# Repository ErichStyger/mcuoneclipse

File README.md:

mcuoneclipse
============

McuOnEclipse Processor Expert components and example projects.
C:\ProgramData\Processor Expert\CWMCU_PE5_00\beans

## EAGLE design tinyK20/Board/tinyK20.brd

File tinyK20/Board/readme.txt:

tinyK20 project files for Eagle CAD.
Links:
- https://mcuoneclipse.com/category/boards/tinyk20/
- https://mcuoneclipse.com/2015/11/17/production-tinyk20-boards-arrived/
- https://mcuoneclipse.com/2015/06/17/tinyk20-new-board-with-micro-sd-card/

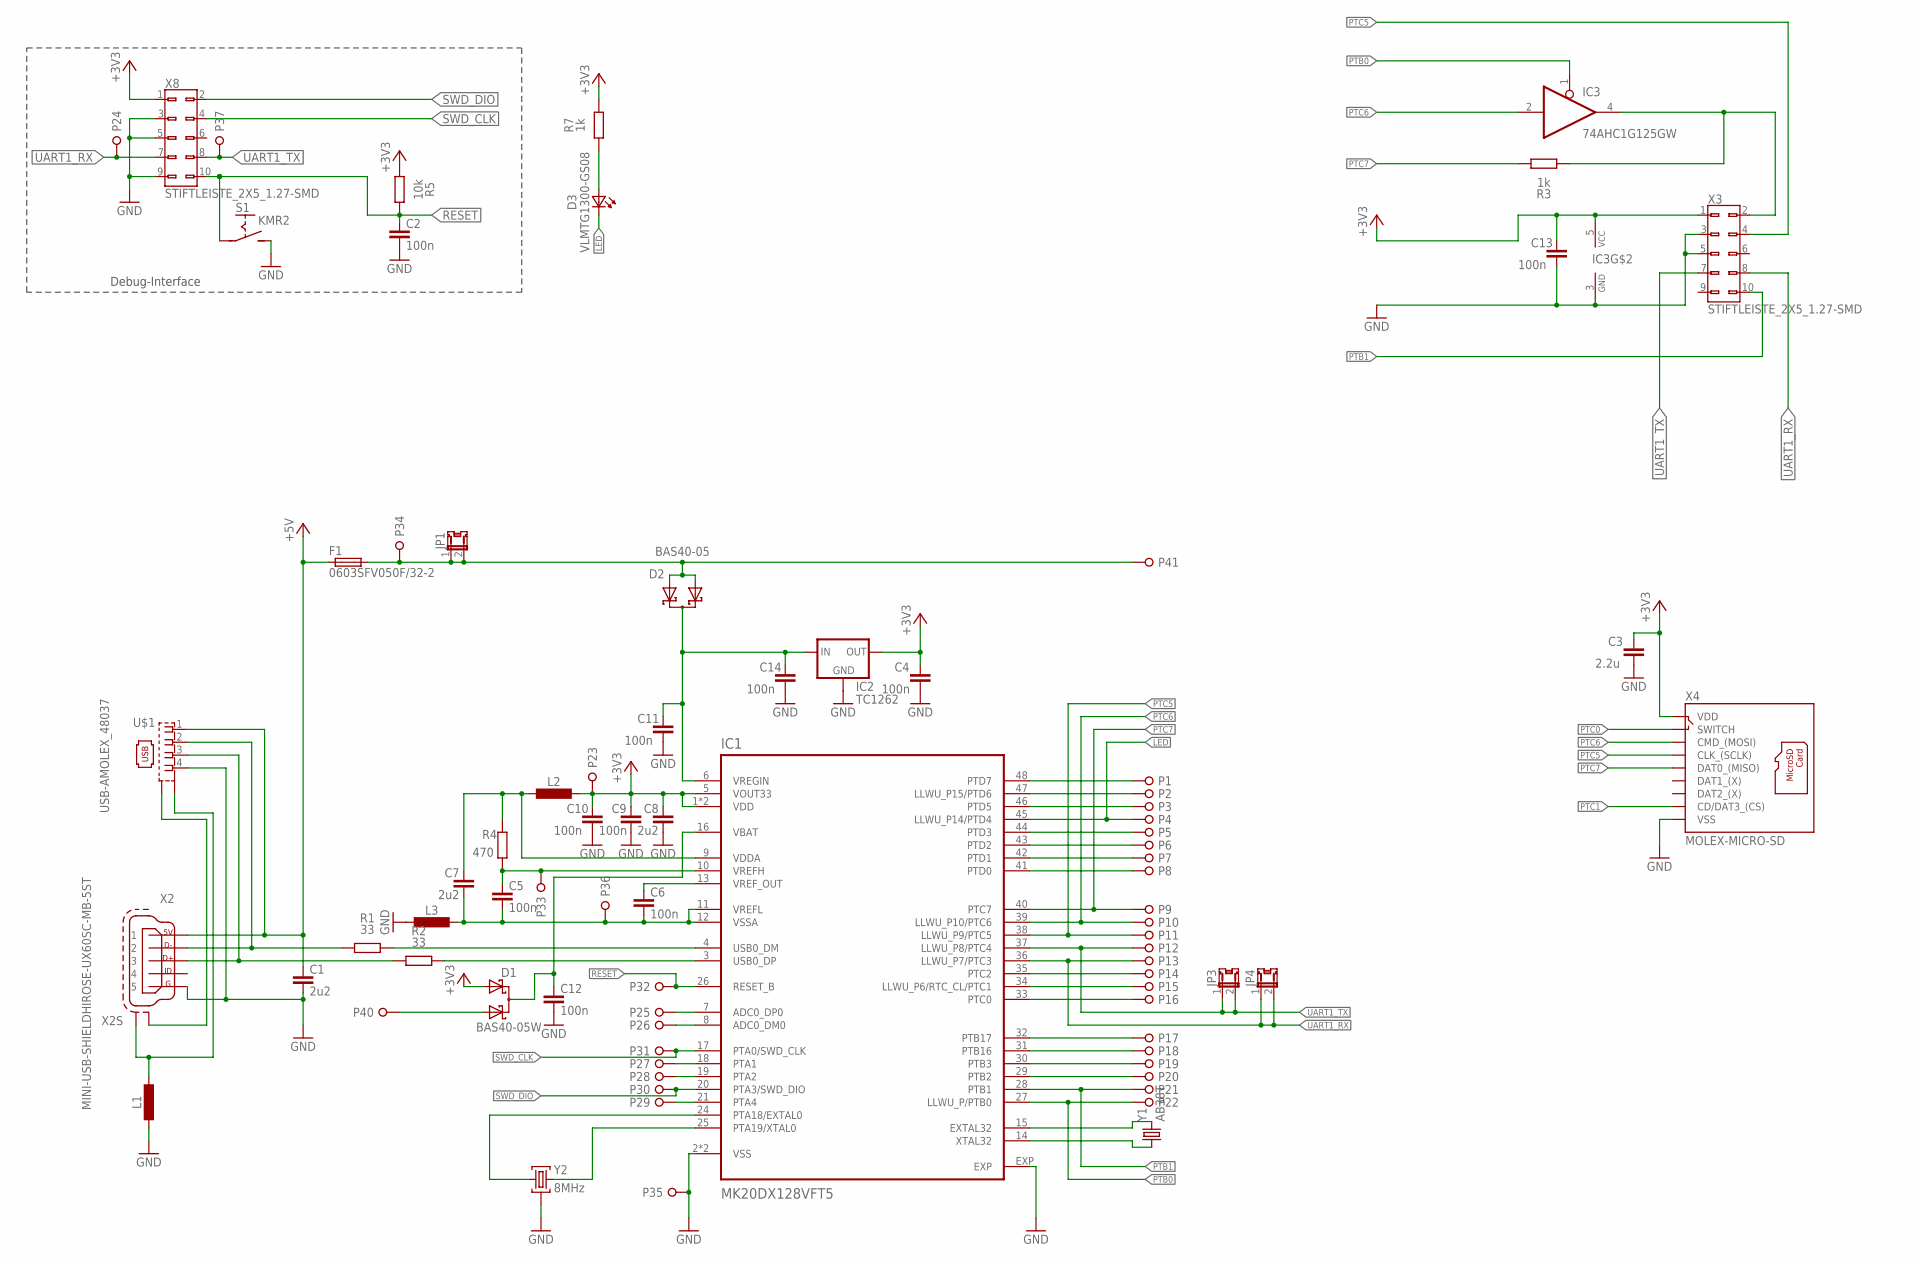
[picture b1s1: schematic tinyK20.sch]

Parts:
C1, C7, C8: 2u2; C0603-R
C2, C4, C5, C6, C9, C10, C11, C12, C13, C14: 100n; C0603-R
C3: 2.2u; C0603-R
D1: BAS40-05W; SOT-323
D2: BAS40-05; SOT-23
D3: VLMTG1300-GS08; D0603-R
F1: 0603SFV050F/32-2; 0603-R
IC1: MK20DX128VFT5; QFN48
IC2: TC1262; SOT-223
IC3: 74AHC1G125GW; SOT-353
JP1, JP3, JP4: JP1-SMD-1.2X1.8; JP-SMD-1.2X1.8
L1, L2, L3: L; L0603-R
P1, P2, P3, P4, P5, P6, P7, P8, P9, P10, P11, P12, P13, P14, P15, P16, P17, P18, P19, P20, P21, P22, P23, P24, P25, P26, P27, P28, P29, P30, P31, P32, P33, P34, P35, P36, P37, P40, P41: SOLDERPAD; SOLDERPAD_TH_0.9
R1, R2: 33; R0603-R
R3, R7: 1k; R0603-R
R4: 470; R0603-R
R5: 10k; R0603-R
S1: KMR2; SWITCH-KMR-SERIES
U$1: USB-AMOLEX_48037; USB-A-MOLEX_48037
X2: MINI-USB-SHIELDHIROSE-UX60SC-MB-5ST; USB-MINI-B-HORIZ_HIROSE-UX60SC-MB-5ST
X3, X8: STIFTLEISTE_2X5_1.27-SMD; STIFTLEISTE_2X5_1.27_SMD
X4: MOLEX-MICRO-SD; SD-105027-001
Y1: AB38T; CRYSTAL-AB38T
Y2: 8MHz; CSTCE

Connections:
+3V3: C3.1, C4.1, C8.1, C9.1, C10.1, C13.1, D1.1 (A), IC1.1 (VDD), IC1.5 (VOUT33), IC1.22 (VDD), IC2.3 (OUT), IC3.5 (VCC), L2.2, P23.1, R5.1, R7.2, X3.1, X4.P4 (VDD), X8.1
+5V: C1.1, F1.1, U$1.1, X2.1
GND: C1.2, C2.2, C3.2, C4.2, C8.2, C9.2, C10.2, C11.2, C12.2, C13.2, C14.2, IC1.2 (VSS), IC1.23 (VSS), IC1.EXP, IC2.2 (GND), IC2.4 (GND), IC3.3 (GND), L1.1, L3.1, P35.1, S1.3 (S), S1.4 (S), U$1.4, X2.5, X3.3, X3.5, X4.P6 (VSS), X8.3, X8.5, X8.9, Y2.2
LED: D3.2 (K), IC1.45 (LLWU_P14/PTD4), P4.1
unnamed: R1.1, U$1.2, X2.2
unnamed: D1.2 (A), P40.1
unnamed: C5.2, C6.2, C7.2, IC1.11 (VREFL), IC1.12 (VSSA), L3.2, P36.1
unnamed: R2.1, U$1.3, X2.3
unnamed: C6.1, IC1.13 (VREF_OUT)
unnamed: IC1.4 (USB0_DM), R1.2
unnamed: C5.1, IC1.10 (VREFH), P33.1, R4.1
unnamed: IC1.3 (USB0_DP), R2.2
unnamed: IC1.24 (PTA18/EXTAL0), Y2.1
unnamed: IC1.25 (PTA19/XTAL0), Y2.3
unnamed: C7.1, IC1.9 (VDDA), L2.1, R4.2
unnamed: IC1.48 (PTD7), P1.1
unnamed: IC1.47 (LLWU_P15/PTD6), P2.1
unnamed: IC1.46 (PTD5), P3.1
unnamed: U$1.S2A (S2), U$1.S2B (S2), X2.S1
unnamed: C11.1, C14.1, D2.3 (COMMON), IC1.6 (VREGIN), IC2.1 (IN)
unnamed: D3.1 (A), R7.1
unnamed: IC1.44 (PTD3), P5.1
unnamed: C12.1, D1.3 (COMMON), IC1.16 (VBAT)
unnamed: IC1.43 (PTD2), P6.1
unnamed: IC1.42 (PTD1), P7.1
unnamed: IC1.41 (PTD0), P8.1
unnamed: D2.1 (A), D2.2 (A), F1.2, JP1.1, JP1.2, P34.1, P41.1
unnamed: IC3.4 (O), R3.1, X3.2
unnamed: IC1.35 (PTC2), P14.1
unnamed: IC1.32 (PTB17), P17.1
unnamed: IC1.31 (PTB16), P18.1
unnamed: IC1.30 (PTB3), P19.1
unnamed: IC1.29 (PTB2), P20.1
unnamed: IC1.15 (EXTAL32), Y1.2 (3)
unnamed: IC1.14 (XTAL32), Y1.1
unnamed: IC1.21 (PTA4), P29.1
unnamed: IC1.19 (PTA2), P28.1
unnamed: IC1.18 (PTA1), P27.1
unnamed: IC1.8 (ADC0_DM0), P26.1
unnamed: IC1.7 (ADC0_DP0), P25.1
unnamed: L1.2, U$1.S1A (S1), U$1.S1B (S1), X2.S2
PTB0: IC1.27 (LLWU_P/PTB0), IC3.1 (OE), P22.1
PTB1: IC1.28 (PTB1), P21.1, X3.10
PTC0: IC1.33 (PTC0), P16.1, X4.G1 (SWITCH)
PTC1: IC1.34 (LLWU_P6/RTC_CL/PTC1), P15.1, X4.P2 (CD/DAT3_(CS))
PTC5: IC1.38 (LLWU_P9/PTC5), P11.1, X3.4, X4.P5 (CLK_(SCLK))
PTC6: IC1.39 (LLWU_P10/PTC6), IC3.2 (I), P10.1, X4.P3 (CMD_(MOSI))
PTC7: IC1.40 (PTC7), P9.1, R3.2, X4.P7 (DAT0_(MISO))
RESET: C2.1, IC1.26 (RESET_B), P32.1, R5.2, S1.1 (C), S1.2 (C), X8.10
SWD_CLK: IC1.17 (PTA0/SWD_CLK), P31.1, X8.4
SWD_DIO: IC1.20 (PTA3/SWD_DIO), P30.1, X8.2
UART1_RX: IC1.36 (LLWU_P7/PTC3), JP4.1, JP4.2, P13.1, P24.1, X3.8, X8.7
UART1_TX: IC1.37 (LLWU_P8/PTC4), JP3.1, JP3.2, P12.1, P37.1, X3.7, X8.8

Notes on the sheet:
Debug-Interface

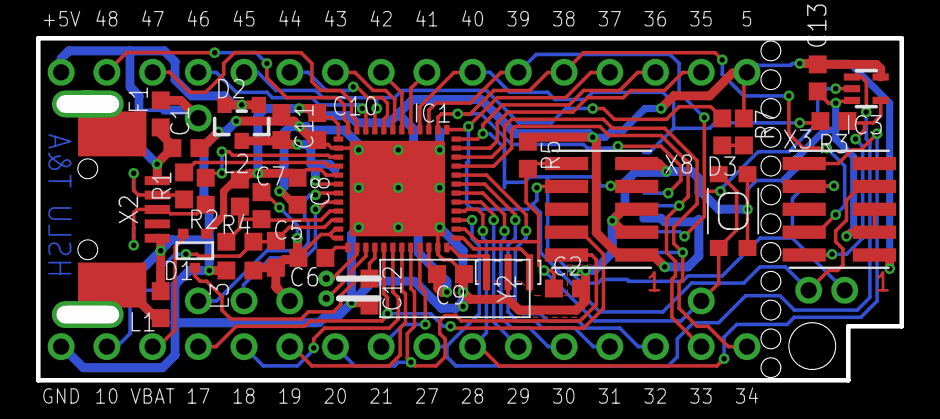
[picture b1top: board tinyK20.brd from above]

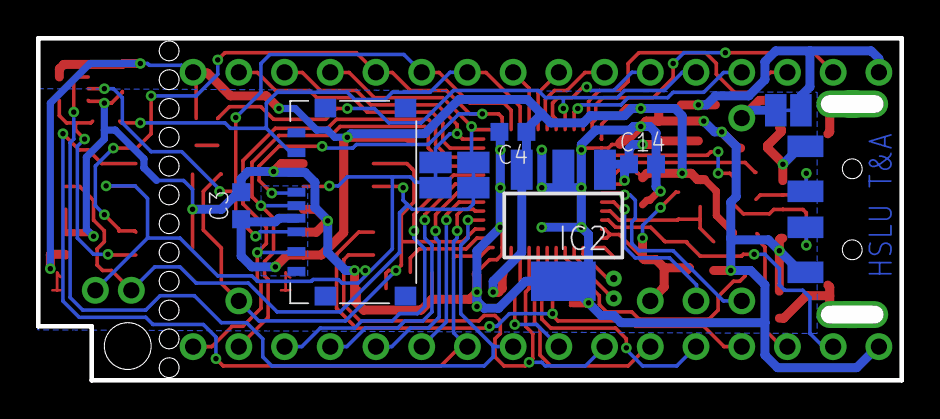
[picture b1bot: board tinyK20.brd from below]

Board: 2 copper layers, 48.0 x 19.0 mm, 80 parts (9 on the bottom side), 53 nets.

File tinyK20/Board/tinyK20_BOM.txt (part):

Part Value                               Device                              Package                               Description                      MFR    MFR_PART-NO   MOUSER_PART-NO   
C1   2u2                                 C0603                               C0603-R                               Capacitor                                                              
C2   100n                                C0603                               C0603-R                               Capacitor                                                              
C3   2.2u                                C0603                               C0603-R                               Capacitor                                                              
C4   100n                                C0603                               C0603-R                               Capacitor                                                              
C5   100n                                C0603                               C0603-R                               Capacitor                                                              
C6   100n                                C0603                               C0603-R                               Capacitor                                                              
C7   2u2                                 C0603                               C0603-R                               Capacitor                                                              
C8   2u2                                 C0603                               C0603-R                               Capacitor                                                              
C9   100n                                C0603                               C0603-R                               Capacitor                                                              
C10  100n                                C0603                               C0603-R                               Capacitor                                                              
C11  100n                                C0603                               C0603-R                               Capacitor                                                              
C12  100n                                C0603                               C0603-R                               Capacitor                                                              
C13  100n                                C0603                               C0603-R                               Capacitor                                                              
C14  100n                                C0603                               C0603-R                               Capacitor                                                              
D1   BAS40-05W                           BAS40-05W                           SOT-323                               Schottky Diode Common Cathode                                          
D2   BAS40-05                            BAS40-05                            SOT-23                                Schottky Diode Common Cathode                                          
D3   VLMTG1300-GS08                      VLMTG1300-GS08                      D0603-R                               Vishay 0603 Highbright ChipLED                                         
F1   0603SFV050F/32-2                    0603SFV050F/32-2                    0603-R                                0603 Very Fast-Acting Chip Fuses                                       
IC1  MK20DX128VFT5                       MK20DX128VFT5                       QFN48                                                                                                        
IC2  TC1262                              TC1262                              SOT-223                               500mA Fixed Output CMOS LDO                                            
IC3  74AHC1G125GW                        74AHC1G125GW                        SOT-353                                                                                                      
JP1  JP1-SMD-1.2X1.8                     JP1-SMD-1.2X1.8                     JP-SMD-1.2X1.8                        JUMPER                                                                 
L1                                       L                                   L0603-R                               Inductor                                                               
L2                                       L                                   L0603-R                               Inductor                                                               
L3                                       L                                   L0603-R                               Inductor                                                               
P1   SOLDERPAD                           SOLDERPAD                           SOLDERPAD_TH_0.9                                                                                             
P2   SOLDERPAD                           SOLDERPAD                           SOLDERPAD_TH_0.9                                                                                             
P3   SOLDERPAD                           SOLDERPAD                           SOLDERPAD_TH_0.9                                                                                             
P4   SOLDERPAD                           SOLDERPAD                           SOLDERPAD_TH_0.9                                                                                             
P5   SOLDERPAD                           SOLDERPAD                           SOLDERPAD_TH_0.9                                                                                             
P6   SOLDERPAD                           SOLDERPAD                           SOLDERPAD_TH_0.9                                                                                             
P7   SOLDERPAD                           SOLDERPAD                           SOLDERPAD_TH_0.9                                                                                             
P8   SOLDERPAD                           SOLDERPAD                           SOLDERPAD_TH_0.9                                                                                             
P9   SOLDERPAD                           SOLDERPAD                           SOLDERPAD_TH_0.9                                                                                             
P10  SOLDERPAD                           SOLDERPAD                           SOLDERPAD_TH_0.9                                                                                             
P11  SOLDERPAD                           SOLDERPAD                           SOLDERPAD_TH_0.9                                                                                             
P12  SOLDERPAD                           SOLDERPAD                           SOLDERPAD_TH_0.9                                                                                             
P13  SOLDERPAD                           SOLDERPAD                           SOLDERPAD_TH_0.9                                                                                             
P14  SOLDERPAD                           SOLDERPAD                           SOLDERPAD_TH_0.9                                                                                             
P15  SOLDERPAD                           SOLDERPAD                           SOLDERPAD_TH_0.9                                                                                             
P16  SOLDERPAD                           SOLDERPAD                           SOLDERPAD_TH_0.9                                                                                             
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
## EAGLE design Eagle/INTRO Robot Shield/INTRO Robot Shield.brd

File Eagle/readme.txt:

readme.txt
----------
This folder contains support/library files for the Eagle layout program.
Place these files inside the lbr subfolder of your Eagle installation.

Libraries:
- Freedom: FRDM-KL25Z footprint
- Bluetooth: HC-05 Bluetooth module (see http://mcuoneclipse.com/2013/02/14/bluetooth-with-the-freedom-board/)

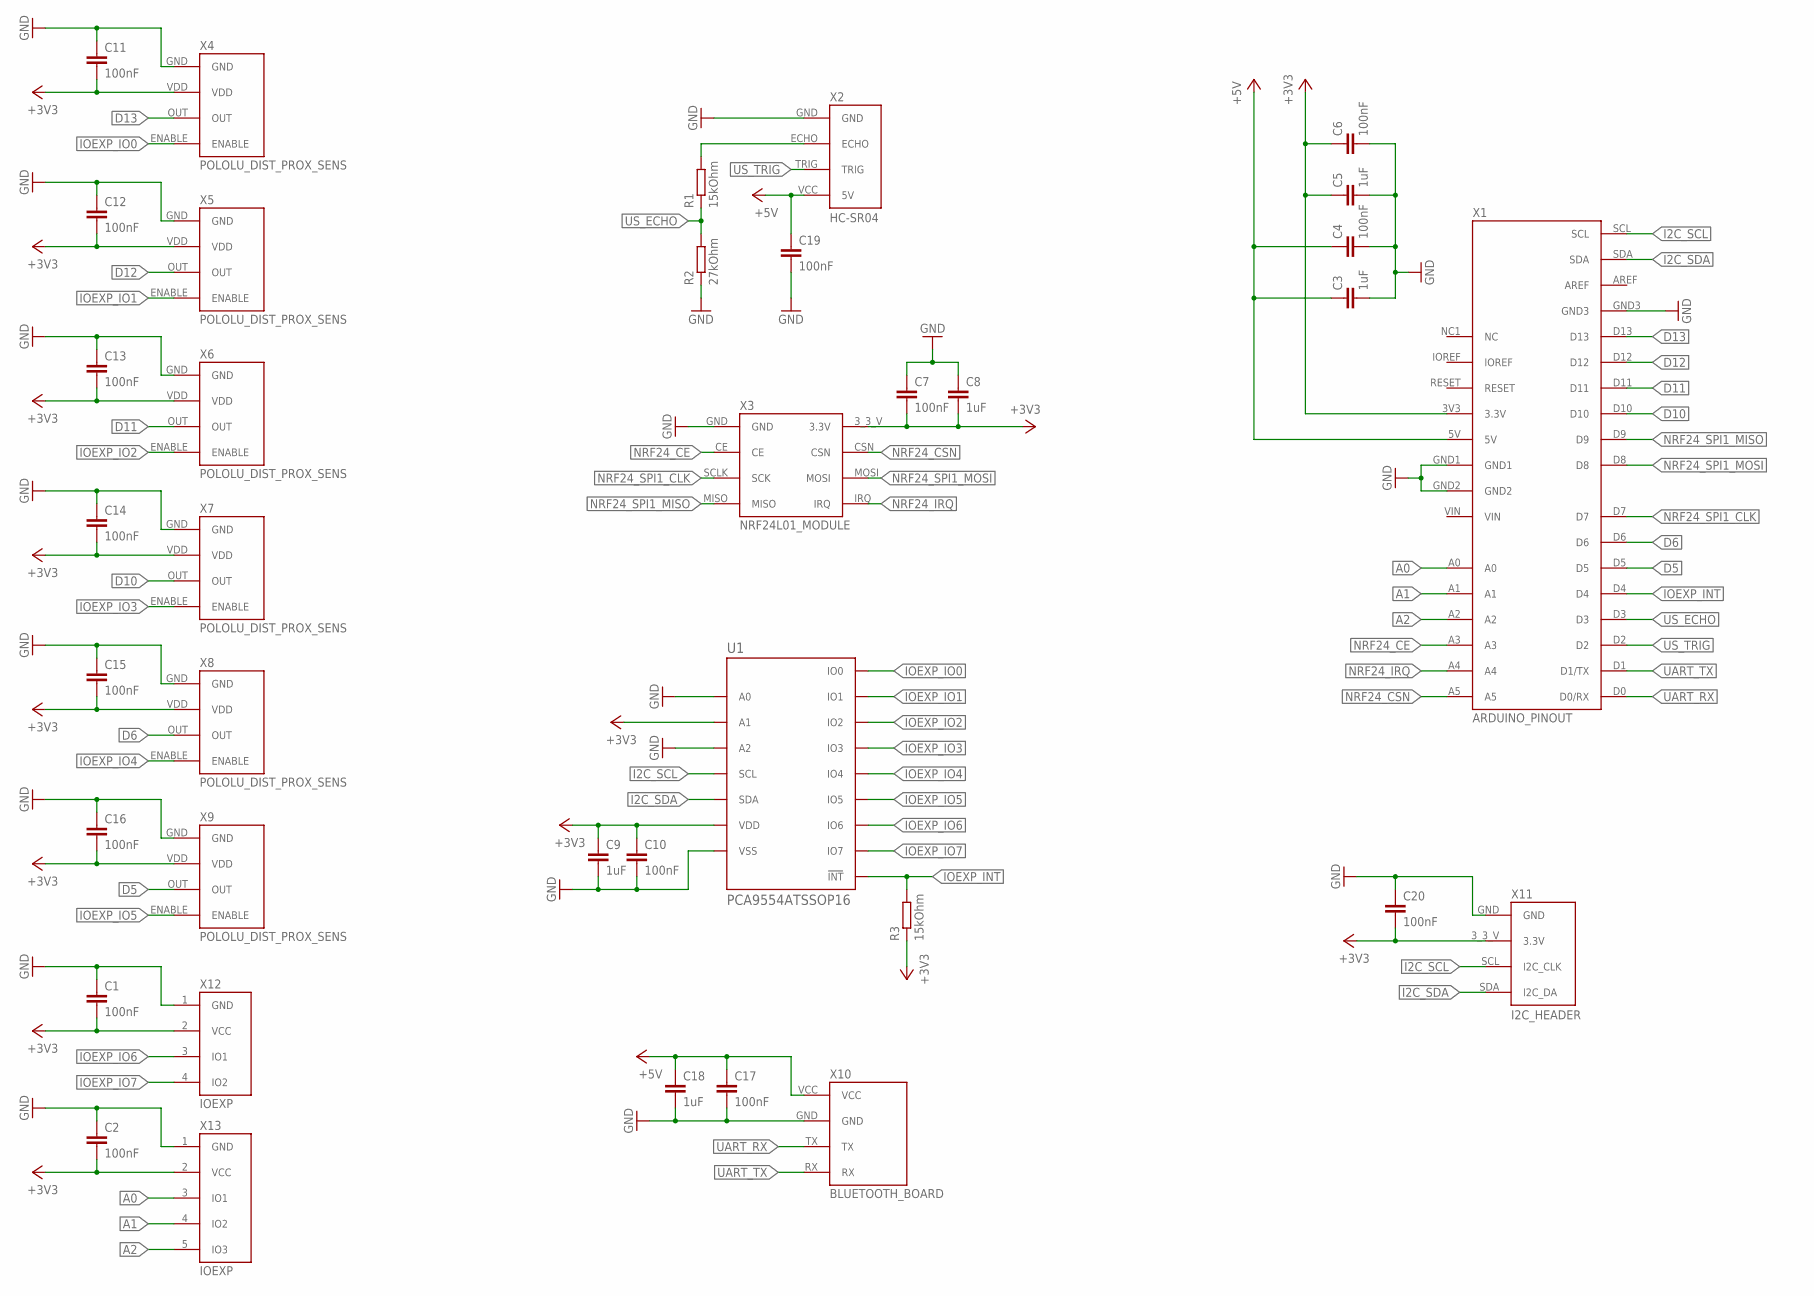
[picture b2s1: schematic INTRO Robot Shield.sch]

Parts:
C1, C2, C4, C6, C7, C10, C11, C12, C13, C14, C15, C16, C17, C19, C20: 100nF; 0805
C3, C5, C8, C9, C18: 1uF; 0805
R1, R3: 15kOhm; 0805
R2: 27kOhm; 0805
U1: PCA9554ATSSOP16; TSSOP16
X1: ARDUINO_PINOUT; ARDUINO_PINOUT_INNER_LABEL
X2: HC-SR04; HC-SR04_FOOTPRINT
X3: NRF24L01_MODULE; NRF24L01_MODULE_FOOTPRINT
X4, X5, X6, X7, X8, X9: POLOLU_DIST_PROX_SENS; POLOLU_DIST_PROX_SENS_FOOTPRINT
X10: BLUETOOTH_BOARD; BT_BOARD_FOOTPRINT
X11: I2C_HEADER; I2C_HEADER_FOOTPRINT
X12: IOEXP; CONNECTORS_STIFTLEISTE_1X4_2.54
X13: IOEXP; CONNECTORS_STIFTLEISTE_1X5_2.54

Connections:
+3V3: C1.2, C2.2, C5.1, C6.1, C7.2, C8.2, C9.1, C10.1, C11.2, C12.2, C13.2, C14.2, C15.2, C16.2, C20.2, R3.1, U1.2 (A1), U1.16 (VDD), X1.3V3 (3.3V), X3.3_3_V (3.3V), X4.VDD, X5.VDD, X6.VDD, X7.VDD, X8.VDD, X9.VDD, X11.3_3_V (3.3V), X12.2 (VCC), X13.2 (VCC)
+5V: C3.1, C4.1, C17.1, C18.1, C19.1, X1.5V, X2.VCC (5V), X10.VCC
A0: X1.A0, X13.3 (IO1)
A1: X1.A1, X13.4 (IO2)
A2: X1.A2, X13.5 (IO3)
D5: X1.D5, X9.OUT
D6: X1.D6, X8.OUT
D10: X1.D10, X7.OUT
D11: X1.D11, X6.OUT
D12: X1.D12, X5.OUT
D13: X1.D13, X4.OUT
GND: C1.1, C2.1, C3.2, C4.2, C5.2, C6.2, C7.1, C8.1, C9.2, C10.2, C11.1, C12.1, C13.1, C14.1, C15.1, C16.1, C17.2, C18.2, C19.2, C20.1, R2.1, U1.1 (A0), U1.3 (A2), U1.8 (VSS), X1.GND1, X1.GND2, X1.GND3, X2.GND, X3.GND, X4.GND, X5.GND, X6.GND, X7.GND, X8.GND, X9.GND, X10.GND, X11.GND, X12.1 (GND), X13.1 (GND)
I2C_SCL: U1.14 (SCL), X1.SCL, X11.SCL (I2C_CLK)
I2C_SDA: U1.15 (SDA), X1.SDA, X11.SDA (I2C_DA)
IOEXP_INT: R3.2, U1.13 (!INT), X1.D4
IOEXP_IO0: U1.4 (IO0), X4.ENABLE
IOEXP_IO1: U1.5 (IO1), X5.ENABLE
IOEXP_IO2: U1.6 (IO2), X6.ENABLE
IOEXP_IO3: U1.7 (IO3), X7.ENABLE
IOEXP_IO4: U1.9 (IO4), X8.ENABLE
IOEXP_IO5: U1.10 (IO5), X9.ENABLE
IOEXP_IO6: U1.11 (IO6), X12.3 (IO1)
IOEXP_IO7: U1.12 (IO7), X12.4 (IO2)
unnamed: R1.2, X2.ECHO
NRF24_CE: X1.A3, X3.CE
NRF24_CSN: X1.A5, X3.CSN
NRF24_IRQ: X1.A4, X3.IRQ
NRF24_SPI1_CLK: X1.D7, X3.SCLK (SCK)
NRF24_SPI1_MISO: X1.D9, X3.MISO
NRF24_SPI1_MOSI: X1.D8, X3.MOSI
UART_RX: X1.D0 (D0/RX), X10.TX
UART_TX: X1.D1 (D1/TX), X10.RX
US_ECHO: R1.1, R2.2, X1.D3
US_TRIG: X1.D2, X2.TRIG

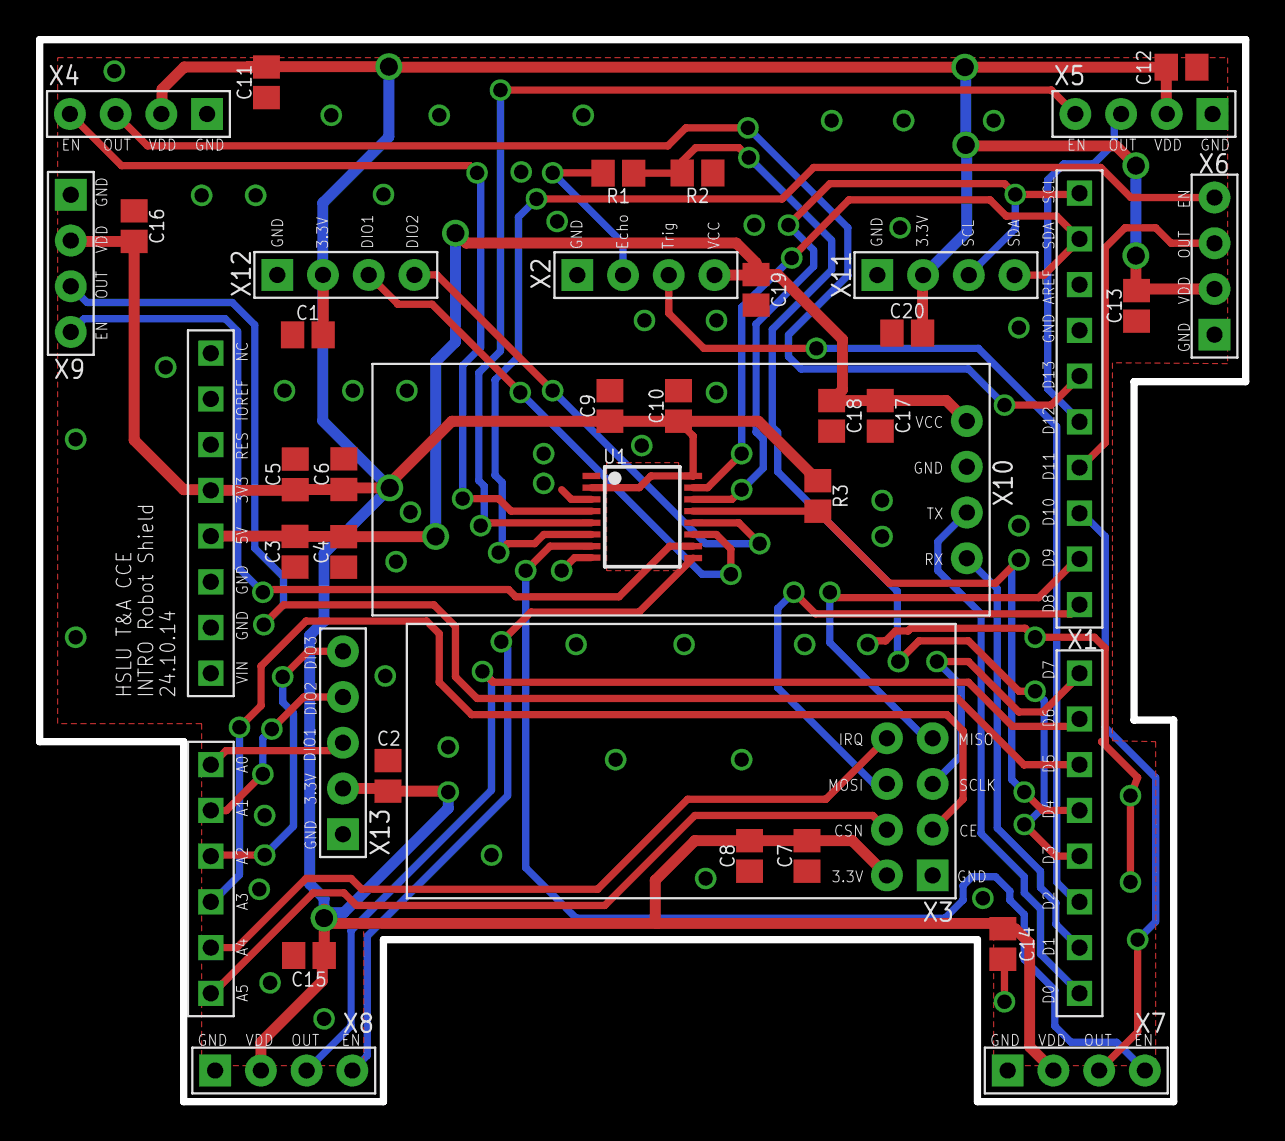
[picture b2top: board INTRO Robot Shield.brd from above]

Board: 2 copper layers, 67.0 x 59.0 mm, 37 parts (0 on the bottom side), 34 nets.

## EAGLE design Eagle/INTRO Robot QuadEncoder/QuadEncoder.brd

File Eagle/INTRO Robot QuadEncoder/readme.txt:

See the following post:
http://mcuoneclipse.com/2014/03/14/new-encoder-pcbs-arrived/
http://mcuoneclipse.com/2014/03/08/processing-the-pololu-motor-shaft-encoders/

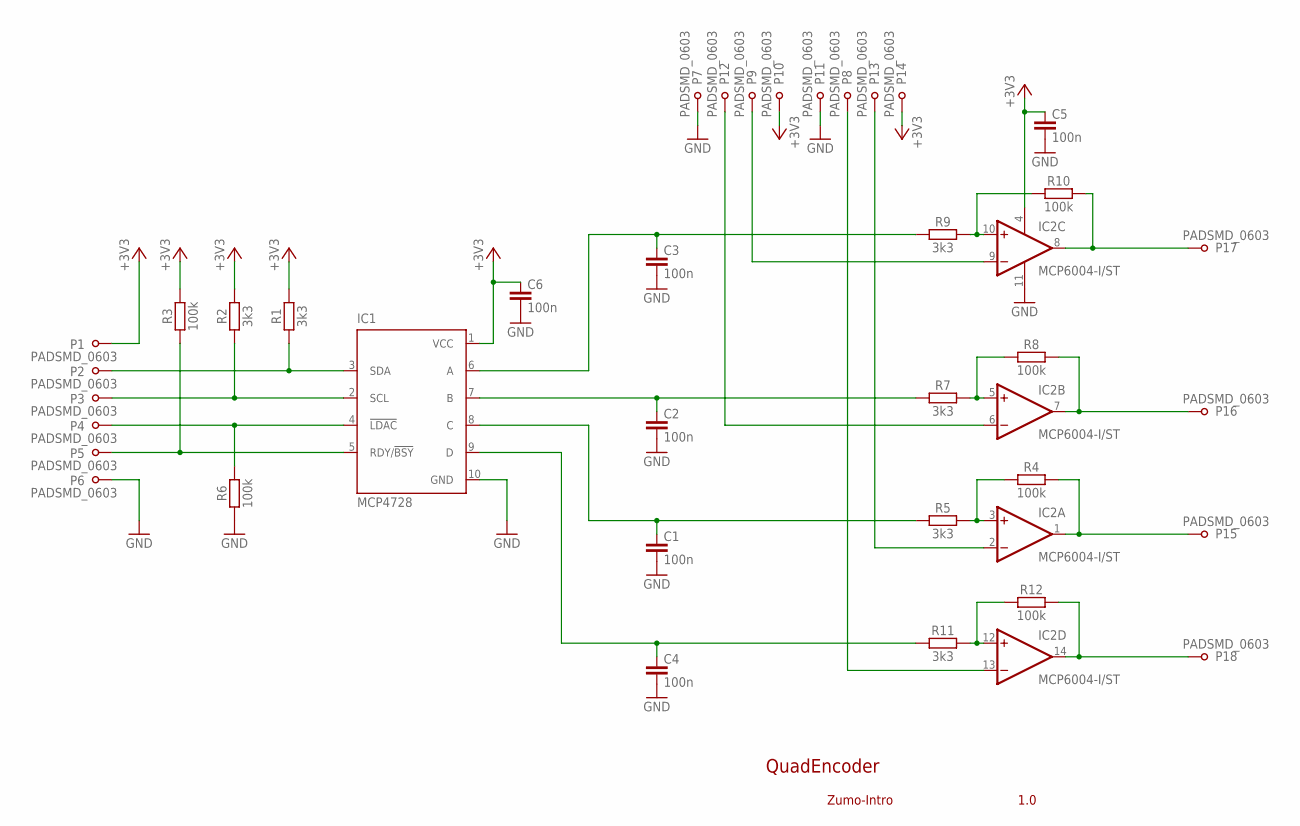
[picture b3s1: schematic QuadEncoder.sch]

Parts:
C1, C2, C3, C4, C5, C6: 100n; C0805-R
IC1: MCP4728; MSOP10
IC2: MCP6004-I/ST; TSSOP14
P1, P2, P3, P4, P5, P6, P7, P8, P9, P10, P11, P12, P13, P14, P15, P16, P17, P18: PADSMD_0603; PAD_SMD_0603
R1, R2, R5, R7, R9, R11: 3k3; R0805-R
R3, R4, R6, R8, R10, R12: 100k; R0805-R

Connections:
+3V3: C5.1, C6.1, IC1.1 (VCC), IC2.4 (V+), P1.1, P10.1, P14.1, R1.2, R2.2, R3.2
GND: C1.2, C2.2, C3.2, C4.2, C5.2, C6.2, IC1.10 (GND), IC2.11 (V-), P6.1, P7.1, P11.1, R6.1
unnamed: IC1.3 (SDA), P2.1, R1.1
unnamed: IC1.2 (SCL), P3.1, R2.1
unnamed: IC1.4 (!LDAC), P4.1, R6.2
unnamed: IC1.5 (RDY/!BSY), P5.1, R3.1
unnamed: C1.1, IC1.8 (C), R5.1
unnamed: IC2.2 (IN-), P13.1
unnamed: IC2.1 (OUT), P15.1, R4.2
unnamed: IC2.3 (IN+), R4.1, R5.2
unnamed: IC2.12 (IN+), R11.2, R12.1
unnamed: IC2.5 (IN+), R7.2, R8.1
unnamed: IC2.7 (OUT), P16.1, R8.2
unnamed: IC2.6 (IN-), P12.1
unnamed: C2.1, IC1.7 (B), R7.1
unnamed: IC2.10 (IN+), R9.2, R10.1
unnamed: IC2.8 (OUT), P17.1, R10.2
unnamed: IC2.9 (IN-), P9.1
unnamed: C3.1, IC1.6 (A), R9.1
unnamed: IC2.14 (OUT), P18.1, R12.2
unnamed: IC2.13 (IN-), P8.1
unnamed: C4.1, IC1.9 (D), R11.1

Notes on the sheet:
QuadEncoder
Zumo-Intro
1.0

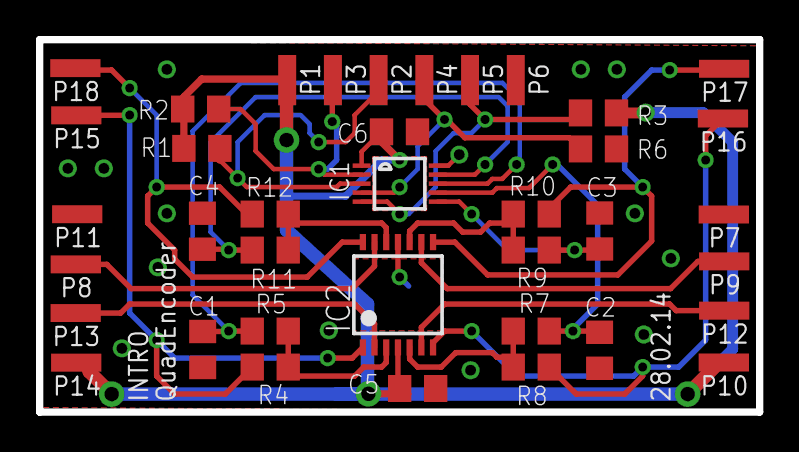
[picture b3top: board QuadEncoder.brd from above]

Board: 2 copper layers, 40.0 x 20.7 mm, 38 parts (0 on the bottom side), 22 nets.

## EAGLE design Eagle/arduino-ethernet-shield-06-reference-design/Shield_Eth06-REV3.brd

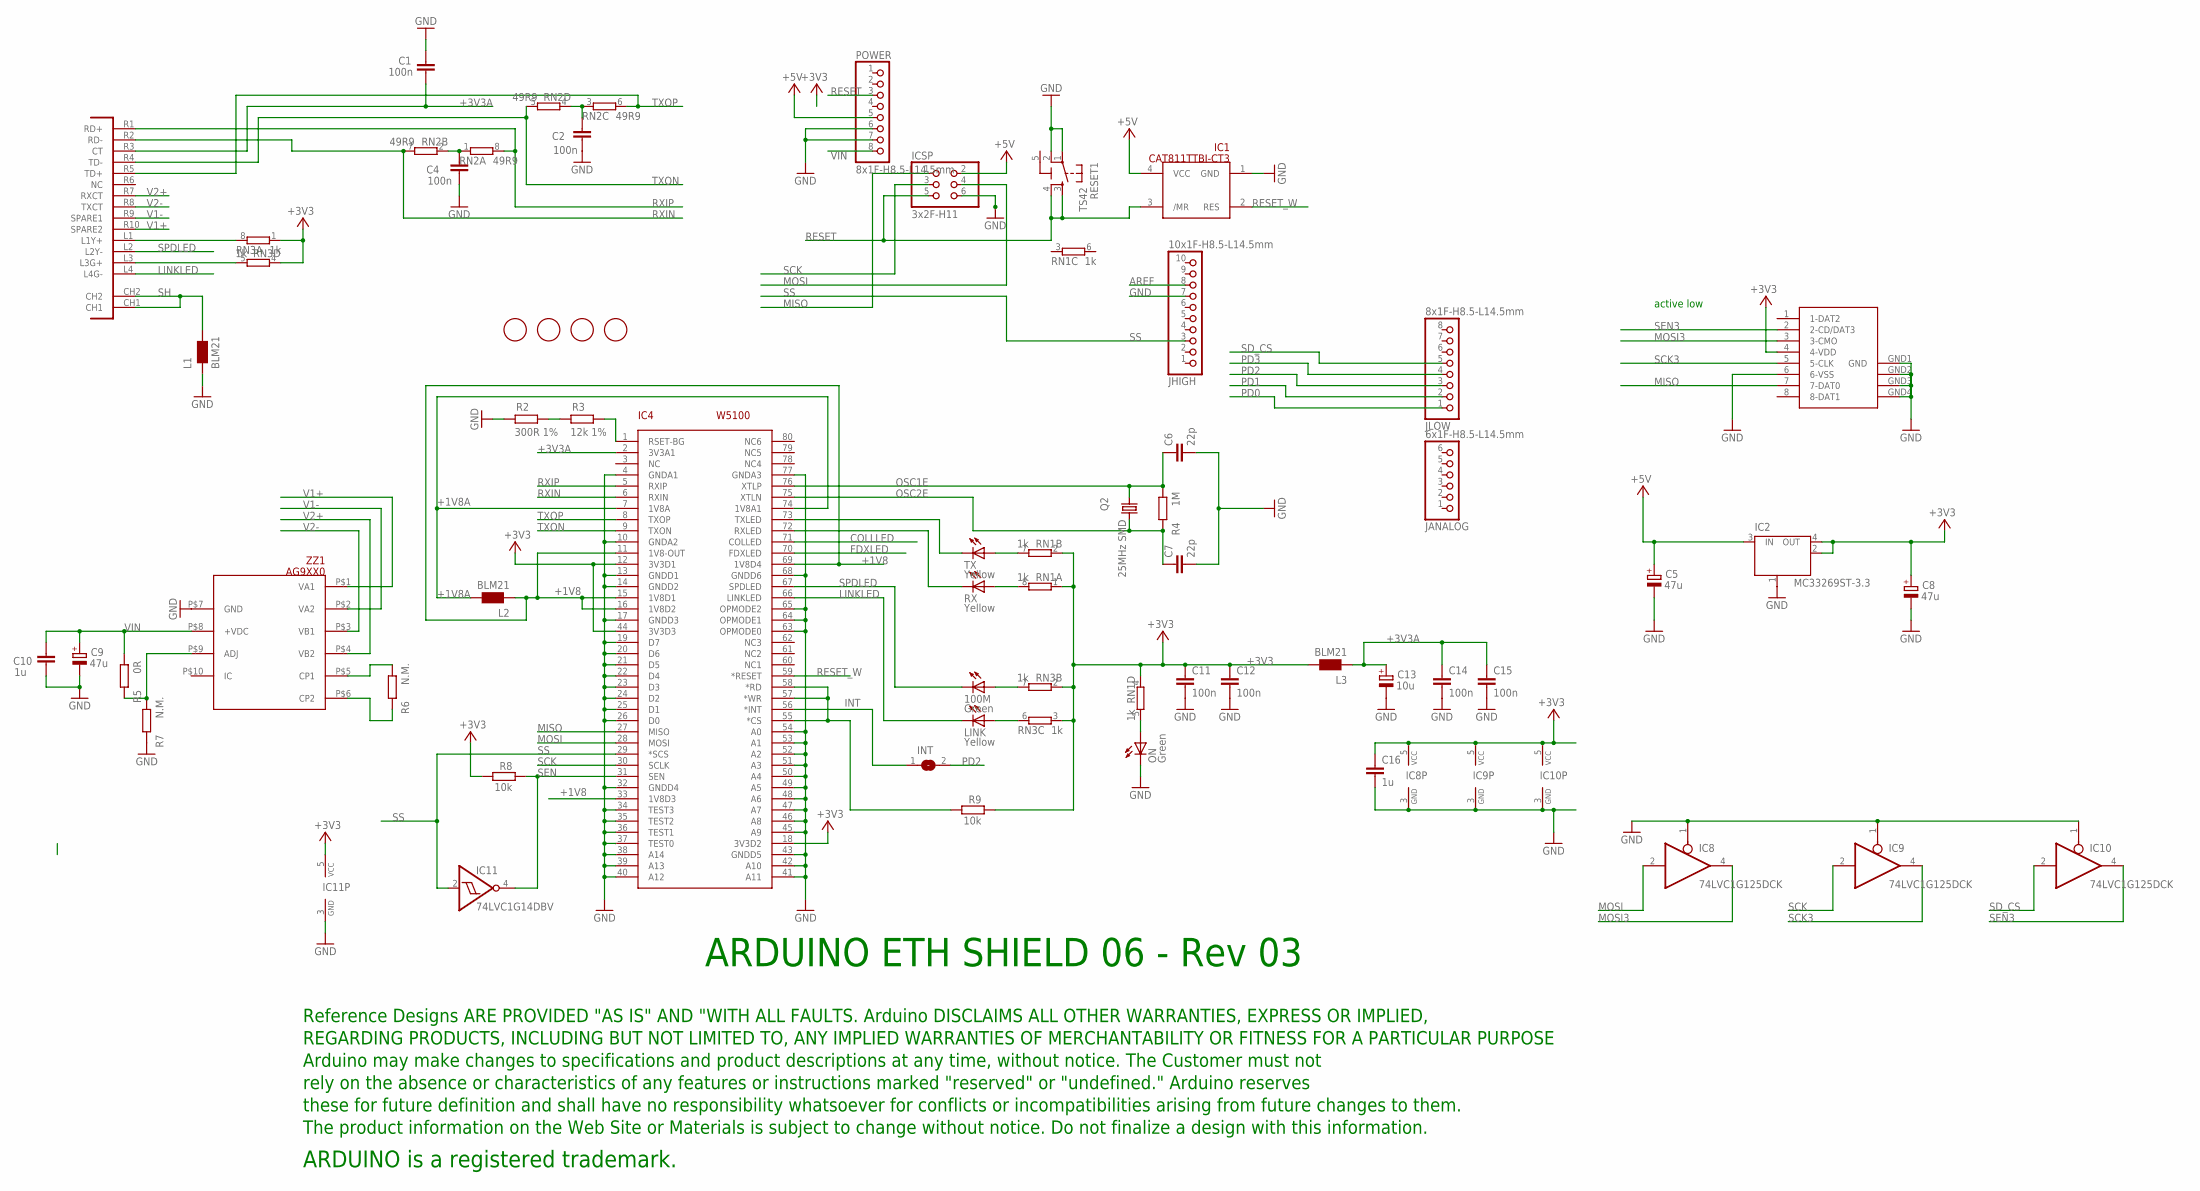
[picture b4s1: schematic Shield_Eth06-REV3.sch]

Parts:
100M: Green; CHIPLED_0805
C1, C2, C4, C11, C12, C14, C15: 100n; C0603-ROUND
C5, C8, C9: 47u; PANASONIC_D
C6, C7: 22p; C0603-ROUND
C10, C16: 1u; C0603-ROUND
C13: 10u; SMC_B
FID1, FID2, FID3, FID4: FIDUCIALMOUNT; FIDUCIA-MOUNT
IC1: CAT811TTBI-CT3; SOT143
IC2: MC33269ST-3.3; SOT223
IC4: W5100; SQFP-S-10X10-80
IC8, IC9, IC10: 74LVC1G125DCK; SC70-5
IC11: 74LVC1G14DBV; SOT23-5
ICSP: 3x2F-H11; 2X03
INT: SJ
JANALOG: 6x1F-H8.5-L14.5mm; 1X06
JHIGH: 10x1F-H8.5-L14.5mm; 1X10
JLOW: 8x1F-H8.5-L14.5mm; 1X08
L1, L2, L3: BLM21; 0805
LINK: Yellow; CHIPLED_0805
ON: Green; CHIPLED_0805
POWER: 8x1F-H8.5-L14.5mm; 1X08
Q2: 25MHz SMD; HC49UP
R2: 300R 1%; R0603-ROUND
R3: 12k 1%; R0603-ROUND
R4: 1M; R0603-ROUND
R5: 0R; R0603-ROUND
R6, R7: N.M.; R0603-ROUND
R8, R9: 10k; R0603-ROUND
RESET1: TS42
RN1, RN3: 1k; CAY16
RN2: 49R9; CAY16
RX: Yellow; CHIPLED_0805
TX: Yellow; CHIPLED_0805
U$1: POE-RJ45
U$2: DISCLAIMER
X1: SDCARD-15TW-8821
ZZ1: AG9XX0; AG9000

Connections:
5-GND: RESET1.5 (5-GND)
+1V8: IC4.11 (1V8-OUT), IC4.15 (1V8D1), IC4.16 (1V8D2), IC4.33 (1V8D3), IC4.69 (1V8D4), L2.1
+1V8A: IC4.7 (1V8A), IC4.74 (1V8A1), L2.2
+3V3: C8.+, C11.1, C12.1, C16.1, IC2.2 (OUT), IC2.4 (OUT), IC4.12 (3V3D1), IC4.18 (3V3D2), IC4.44 (3V3D3), IC8.5 (VCC), IC9.5 (VCC), IC10.5 (VCC), IC11.5 (VCC), L3.2, R8.1, R9.2, RN1.1, RN1.2 (1), RN1.4 (1), RN3.1, RN3.2 (1), RN3.3 (1), RN3.4 (1), X1.4 (4-VDD)
+3V3A: C1.1, C13.+, C14.1, C15.1, IC4.2 (3V3A1), L3.1, U$1.R3 (CT)
+5V: C5.+, IC1.4 (VCC), IC2.3 (IN), ICSP.2, POWER.5
AREF: JHIGH.8
COLLLED: IC4.71 (COLLED)
FDXLED: IC4.70 (FDXLED)
GND: C1.2, C2.1, C4.1, C5.-, C6.2, C7.2, C8.-, C9.-, C10.1, C11.2, C12.2, C13.-, C14.2, C15.2, C16.2, IC1.1 (GND), IC2.1 (GND/ADJ), IC4.4 (GNDA1), IC4.10 (GNDA2), IC4.13 (GNDD1), IC4.14 (GNDD2), IC4.17 (GNDD3), IC4.19 (D7), IC4.20 (D6), IC4.21 (D5), IC4.22 (D4), IC4.23 (D3), IC4.24 (D2), IC4.25 (D1), IC4.26 (D0), IC4.32 (GNDD4), IC4.34 (TEST3), IC4.35 (TEST2), IC4.36 (TEST1), IC4.37 (TEST0), IC4.38 (A14), IC4.39 (A13), IC4.40 (A12), IC4.41 (A11), IC4.42 (A10), IC4.43 (GNDD5), IC4.45 (A9), IC4.46 (A8), IC4.47 (A7), IC4.48 (A6), IC4.49 (A5), IC4.50 (A4), IC4.51 (A3), IC4.52 (A2), IC4.53 (A1), IC4.54 (A0), IC4.63 (OPMODE0), IC4.64 (OPMODE1), IC4.65 (OPMODE2), IC4.68 (GNDD6), IC4.77 (GNDA3), IC8.1 (OE), IC8.3 (GND), IC9.1 (OE), IC9.3 (GND), IC10.1 (OE), IC10.3 (GND), IC11.3 (GND), ICSP.6, JHIGH.7, L1.1, ON.C, POWER.6, POWER.7, R2.2, R7.2, RESET1.1, RESET1.2, X1.6 (6-VSS), X1.GND1 (GND), X1.GND2 (GND1), X1.GND3 (GND2), X1.GND4 (GND3), ZZ1.P$7 (GND)
INT: IC4.56 (*INT), INT.1
LINKLED: IC4.66 (LINKLED), LINK.C, U$1.L4 (L4G-)
MISO: IC4.27 (MISO), ICSP.1, X1.7 (7-DAT0)
MOSI: IC4.28 (MOSI), IC8.2 (I), ICSP.4
MOSI3: IC8.4 (O), X1.3 (3-CMO)
unnamed: RN3.5 (2), U$1.L3 (L3G+)
unnamed: RN3.8 (2), U$1.L1 (L1Y+)
unnamed: IC4.73 (TXLED), TX.C
unnamed: IC4.72 (RXLED), RX.C
unnamed: ON.A, RN1.5 (2)
unnamed: RN1.7 (2), TX.A
unnamed: C2.2, RN2.3 (1), RN2.4 (1)
unnamed: RN1.8 (2), RX.A
unnamed: 100M.A, RN3.7 (2)
unnamed: LINK.A, RN3.6 (2)
unnamed: C4.2, RN2.1, RN2.2 (1)
unnamed: R2.1, R3.2
unnamed: IC4.1 (RSET-BG), R3.1
unnamed: R6.1, ZZ1.P$5 (CP1)
unnamed: R6.2, ZZ1.P$6 (CP2)
unnamed: R5.2, R7.1, ZZ1.P$9 (ADJ)
unnamed: IC4.55 (*CS), IC4.57 (*WR), IC4.58 (*RD), R9.1
OSC1E: C6.1, IC4.76 (XTLP), Q2.1, R4.1
OSC2E: C7.1, IC4.75 (XTLN), Q2.2, R4.2
PD0: JLOW.1
PD1: JLOW.2
PD2: INT.2, JLOW.3
PD3: JLOW.4
RESET: IC1.3 (/MR), ICSP.5, POWER.3, RESET1.3, RESET1.4
RESET_W: IC1.2 (RES), IC4.59 (*RESET)
RXIN: IC4.6 (RXIN), RN2.7 (2), U$1.R2 (RD-)
RXIP: IC4.5 (RXIP), RN2.8 (2), U$1.R1 (RD+)
SCK: IC4.30 (SCLK), IC9.2 (I), ICSP.3
SCK3: IC9.4 (O), X1.5 (5-CLK)
SD_CS: IC10.2 (I), JLOW.5
SEN: IC4.31 (SEN), IC11.4 (O), R8.2
SEN3: IC10.4 (O), X1.2 (2-CD/DAT3)
SH: L1.2, U$1.CH1, U$1.CH2
SPDLED: 100M.C, IC4.67 (SPDLED), U$1.L2 (L2Y-)
SS: IC4.29 (*SCS), IC11.2 (I), JHIGH.3
TXON: IC4.9 (TXON), RN2.5 (2), U$1.R4 (TD-)
TXOP: IC4.8 (TXOP), RN2.6 (2), U$1.R5 (TD+)
V1+: U$1.R10 (SPARE2), ZZ1.P$1 (VA1)
V1-: U$1.R9 (SPARE1), ZZ1.P$2 (VA2)
V2+: U$1.R7 (RXCT), ZZ1.P$4 (VB2)
V2-: U$1.R8 (TXCT), ZZ1.P$3 (VB1)
VIN: C9.+, C10.2, POWER.8, R5.1, ZZ1.P$8 (+VDC)

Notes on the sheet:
ARDUINO ETH SHIELD 06 - Rev 03
active low
